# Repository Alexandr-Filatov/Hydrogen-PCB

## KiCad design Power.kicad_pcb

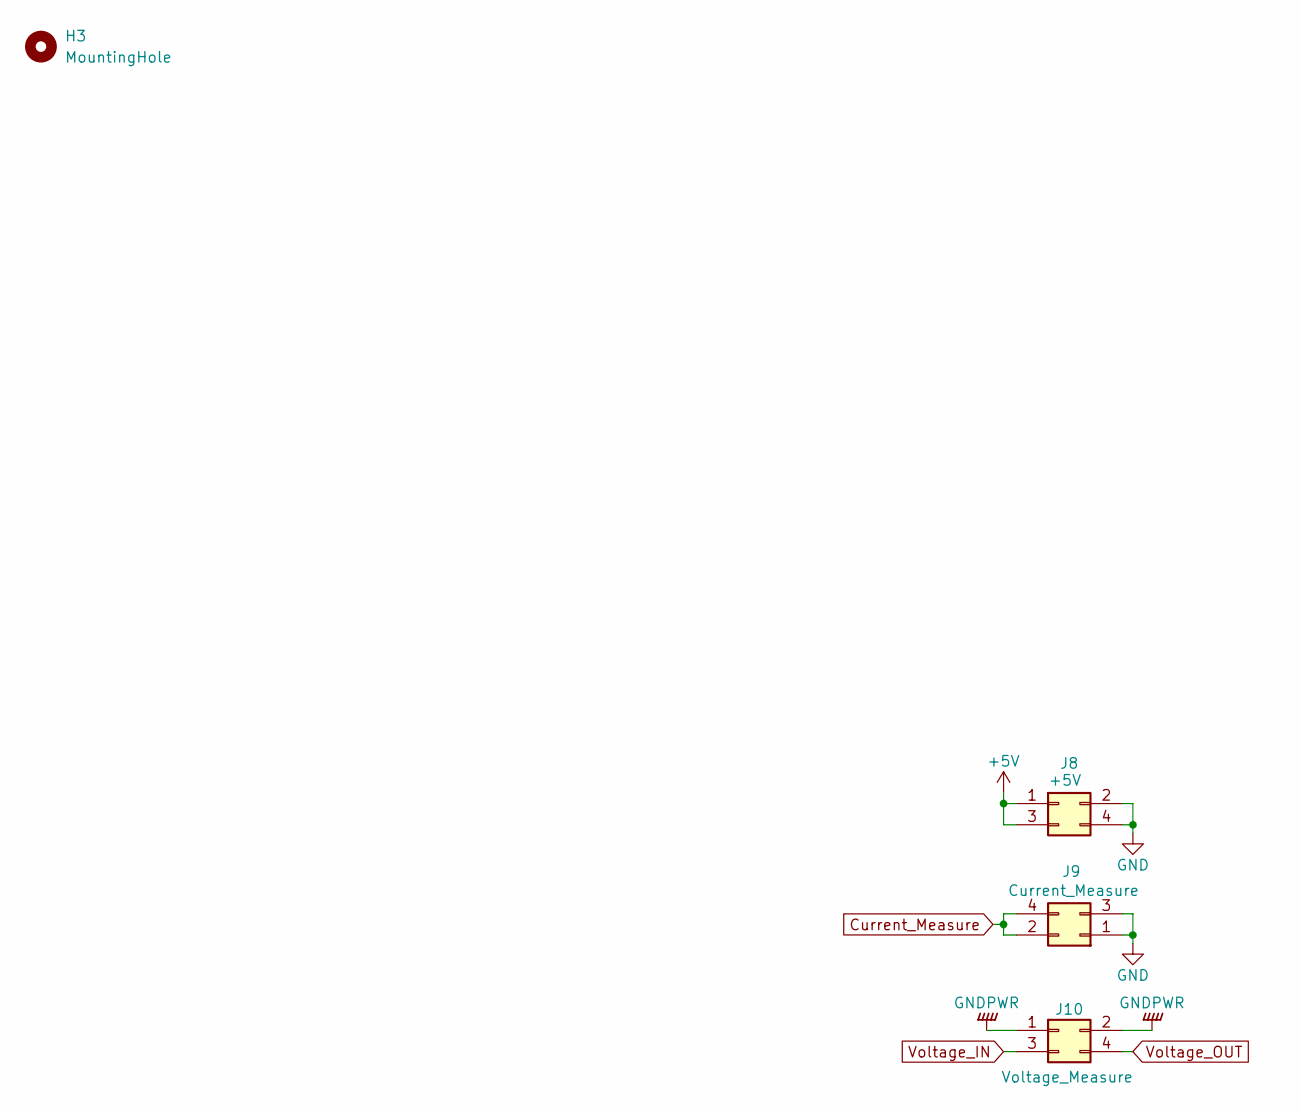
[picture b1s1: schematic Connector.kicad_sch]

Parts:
H3: MountingHole; MountingHole_3.2mm_M3
J8: +5V; Molex_Micro-Fit_3.0_43045-0412_2x02_P3.00mm_Vertical
J9: Current_Measure; Molex_Micro-Fit_3.0_43045-0412_2x02_P3.00mm_Vertical
J10: Voltage_Measure; Molex_Micro-Fit_3.0_43045-0412_2x02_P3.00mm_Vertical

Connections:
+5V: J8.1, J8.3; also elsewhere on the board
Current_Measure: J9.2, J9.4; also elsewhere on the board
GND: J8.2, J8.4, J9.1, J9.3; also elsewhere on the board
GNDPWR: J10.1, J10.2; also elsewhere on the board
Voltage_IN: J10.3; also elsewhere on the board
Voltage_OUT: J10.4; also elsewhere on the board

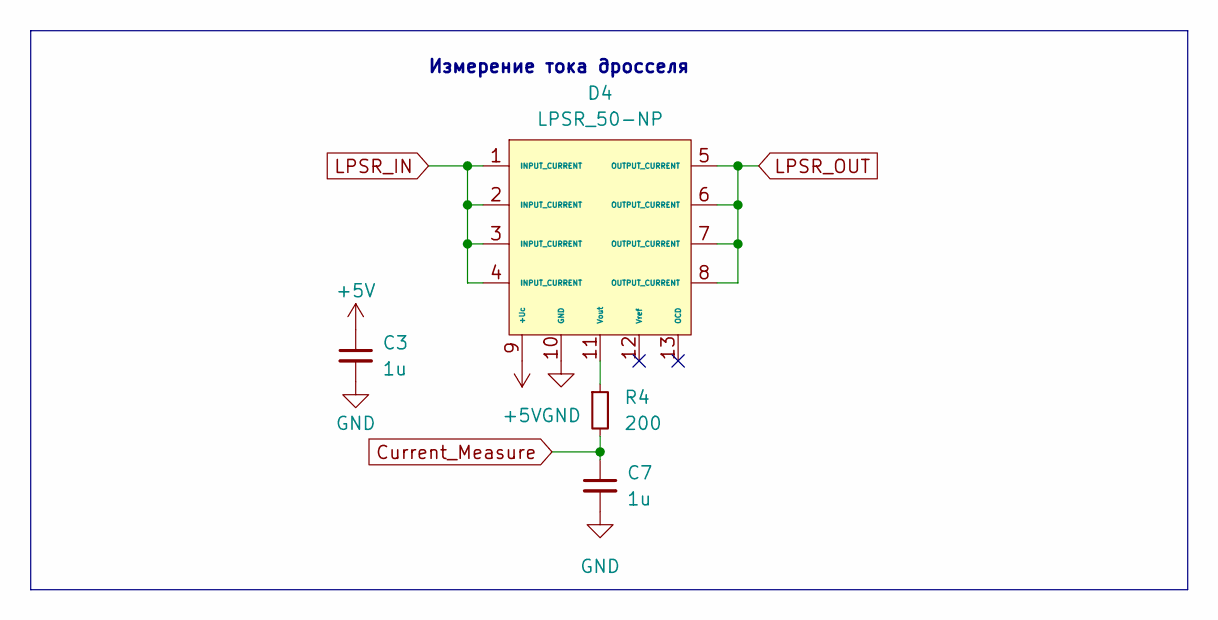
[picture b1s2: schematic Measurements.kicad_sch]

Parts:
C3, C7: 1u; C_0805_2012Metric_Pad1.18x1.45mm_HandSolder
D4: LPSR_50-NP; LPSR_50
R4: 200; R_0805_2012Metric_Pad1.20x1.40mm_HandSolder

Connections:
+5V: C3.1, D4.9 (+Uc); also elsewhere on the board
Current_Measure: C7.1, R4.2; also elsewhere on the board
GND: C3.2, C7.2, D4.10 (GND); also elsewhere on the board
LPSR_IN: D4.1 (INPUT_CURRENT), D4.2 (INPUT_CURRENT), D4.3 (INPUT_CURRENT), D4.4 (INPUT_CURRENT); also elsewhere on the board
LPSR_OUT: D4.5 (OUTPUT_CURRENT), D4.6 (OUTPUT_CURRENT), D4.7 (OUTPUT_CURRENT), D4.8 (OUTPUT_CURRENT); also elsewhere on the board
unnamed: D4.11 (Vout), R4.1

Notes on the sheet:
Измерение тока дросселя

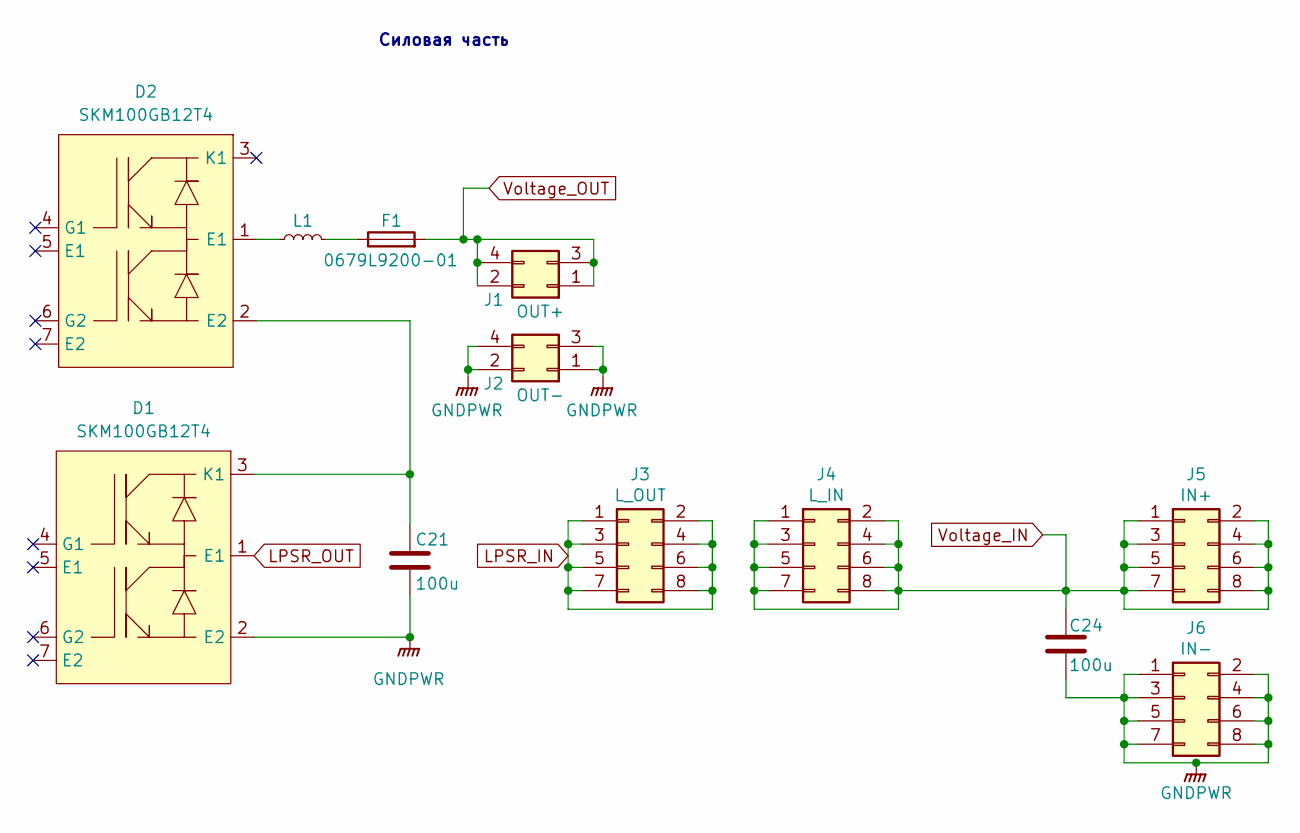
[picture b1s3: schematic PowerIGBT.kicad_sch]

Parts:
C21, C24: 100u; C4AE
D1, D2: SKM100GB12T4; SEMITRANS_2
F1: 0679L9200-01; Fuse_2512_6332Metric_Pad1.52x3.35mm_HandSolder
J1: OUT+; Molex_Micro-Fit_3.0_43045-0412_2x02_P3.00mm_Vertical
J2: OUT-; Molex_Micro-Fit_3.0_43045-0412_2x02_P3.00mm_Vertical
J3: L_OUT; Molex_Micro-Fit_3.0_43045-0812_2x04_P3.00mm_Vertical
J4: L_IN; Molex_Micro-Fit_3.0_43045-0812_2x04_P3.00mm_Vertical
J5: IN+; Molex_Micro-Fit_3.0_43045-0812_2x04_P3.00mm_Vertical
J6: IN-; Molex_Micro-Fit_3.0_43045-0812_2x04_P3.00mm_Vertical
L1: L_Small; Wurth

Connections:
GNDPWR: C21.2, C24.2, D1.2 (E2), J2.1, J2.2, J2.3, J2.4, J6.1, J6.2, J6.3, J6.4, J6.5, J6.6, J6.7, J6.8; also elsewhere on the board
LPSR_IN: J3.1, J3.2, J3.3, J3.4, J3.5, J3.6, J3.7, J3.8; also elsewhere on the board
LPSR_OUT: D1.1 (E1); also elsewhere on the board
unnamed: C21.1, D1.3 (K1), D2.2 (E2)
unnamed: D2.1 (E1), L1.1
unnamed: F1.1, L1.2
Voltage_IN: C24.1, J4.1, J4.2, J4.3, J4.4, J4.5, J4.6, J4.7, J4.8, J5.1, J5.2, J5.3, J5.4, J5.5, J5.6, J5.7, J5.8; also elsewhere on the board
Voltage_OUT: F1.2, J1.1, J1.2, J1.3, J1.4; also elsewhere on the board

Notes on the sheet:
Силовая часть

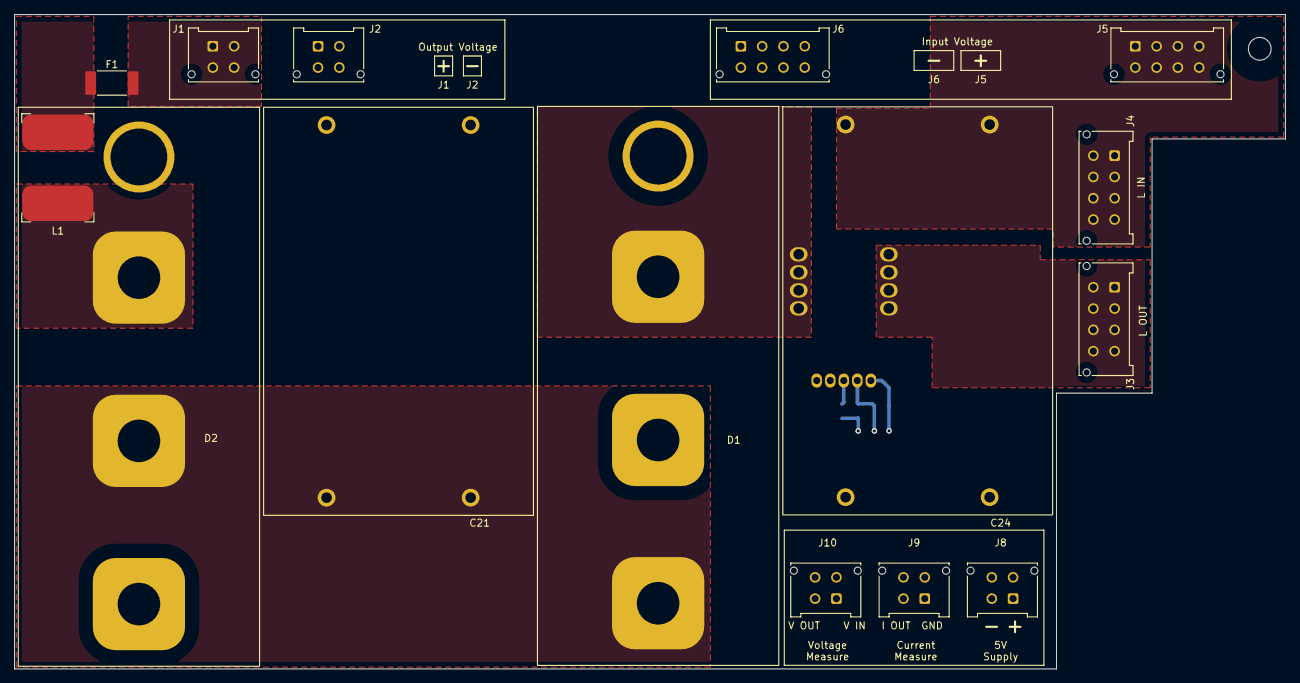
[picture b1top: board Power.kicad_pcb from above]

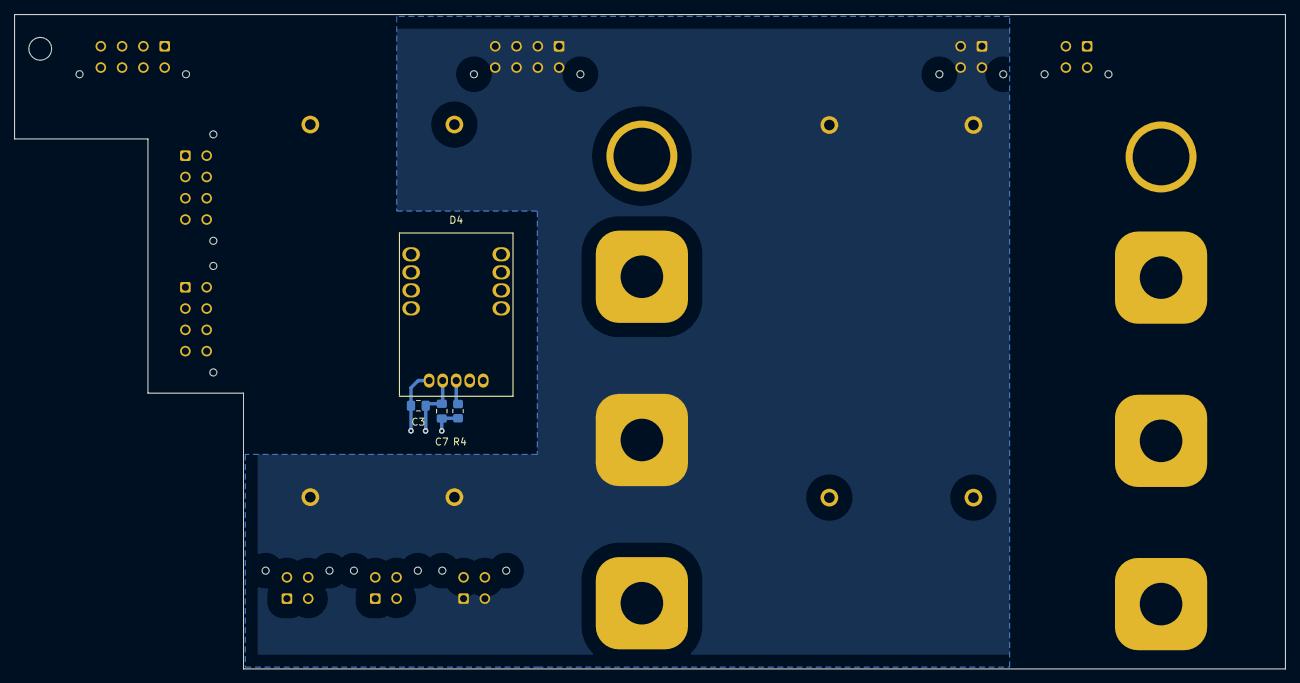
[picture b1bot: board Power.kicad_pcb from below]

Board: 4 copper layers, 179.1 x 92.2 mm, 20 parts (4 on the bottom side), 12 nets.

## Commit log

2022-05-16 VER1.0
2022-05-17 VER2.0
2022-05-27 Готовый вариант
2022-05-27 Поменял предохранитель
2022-06-02 Первая версия в производство
